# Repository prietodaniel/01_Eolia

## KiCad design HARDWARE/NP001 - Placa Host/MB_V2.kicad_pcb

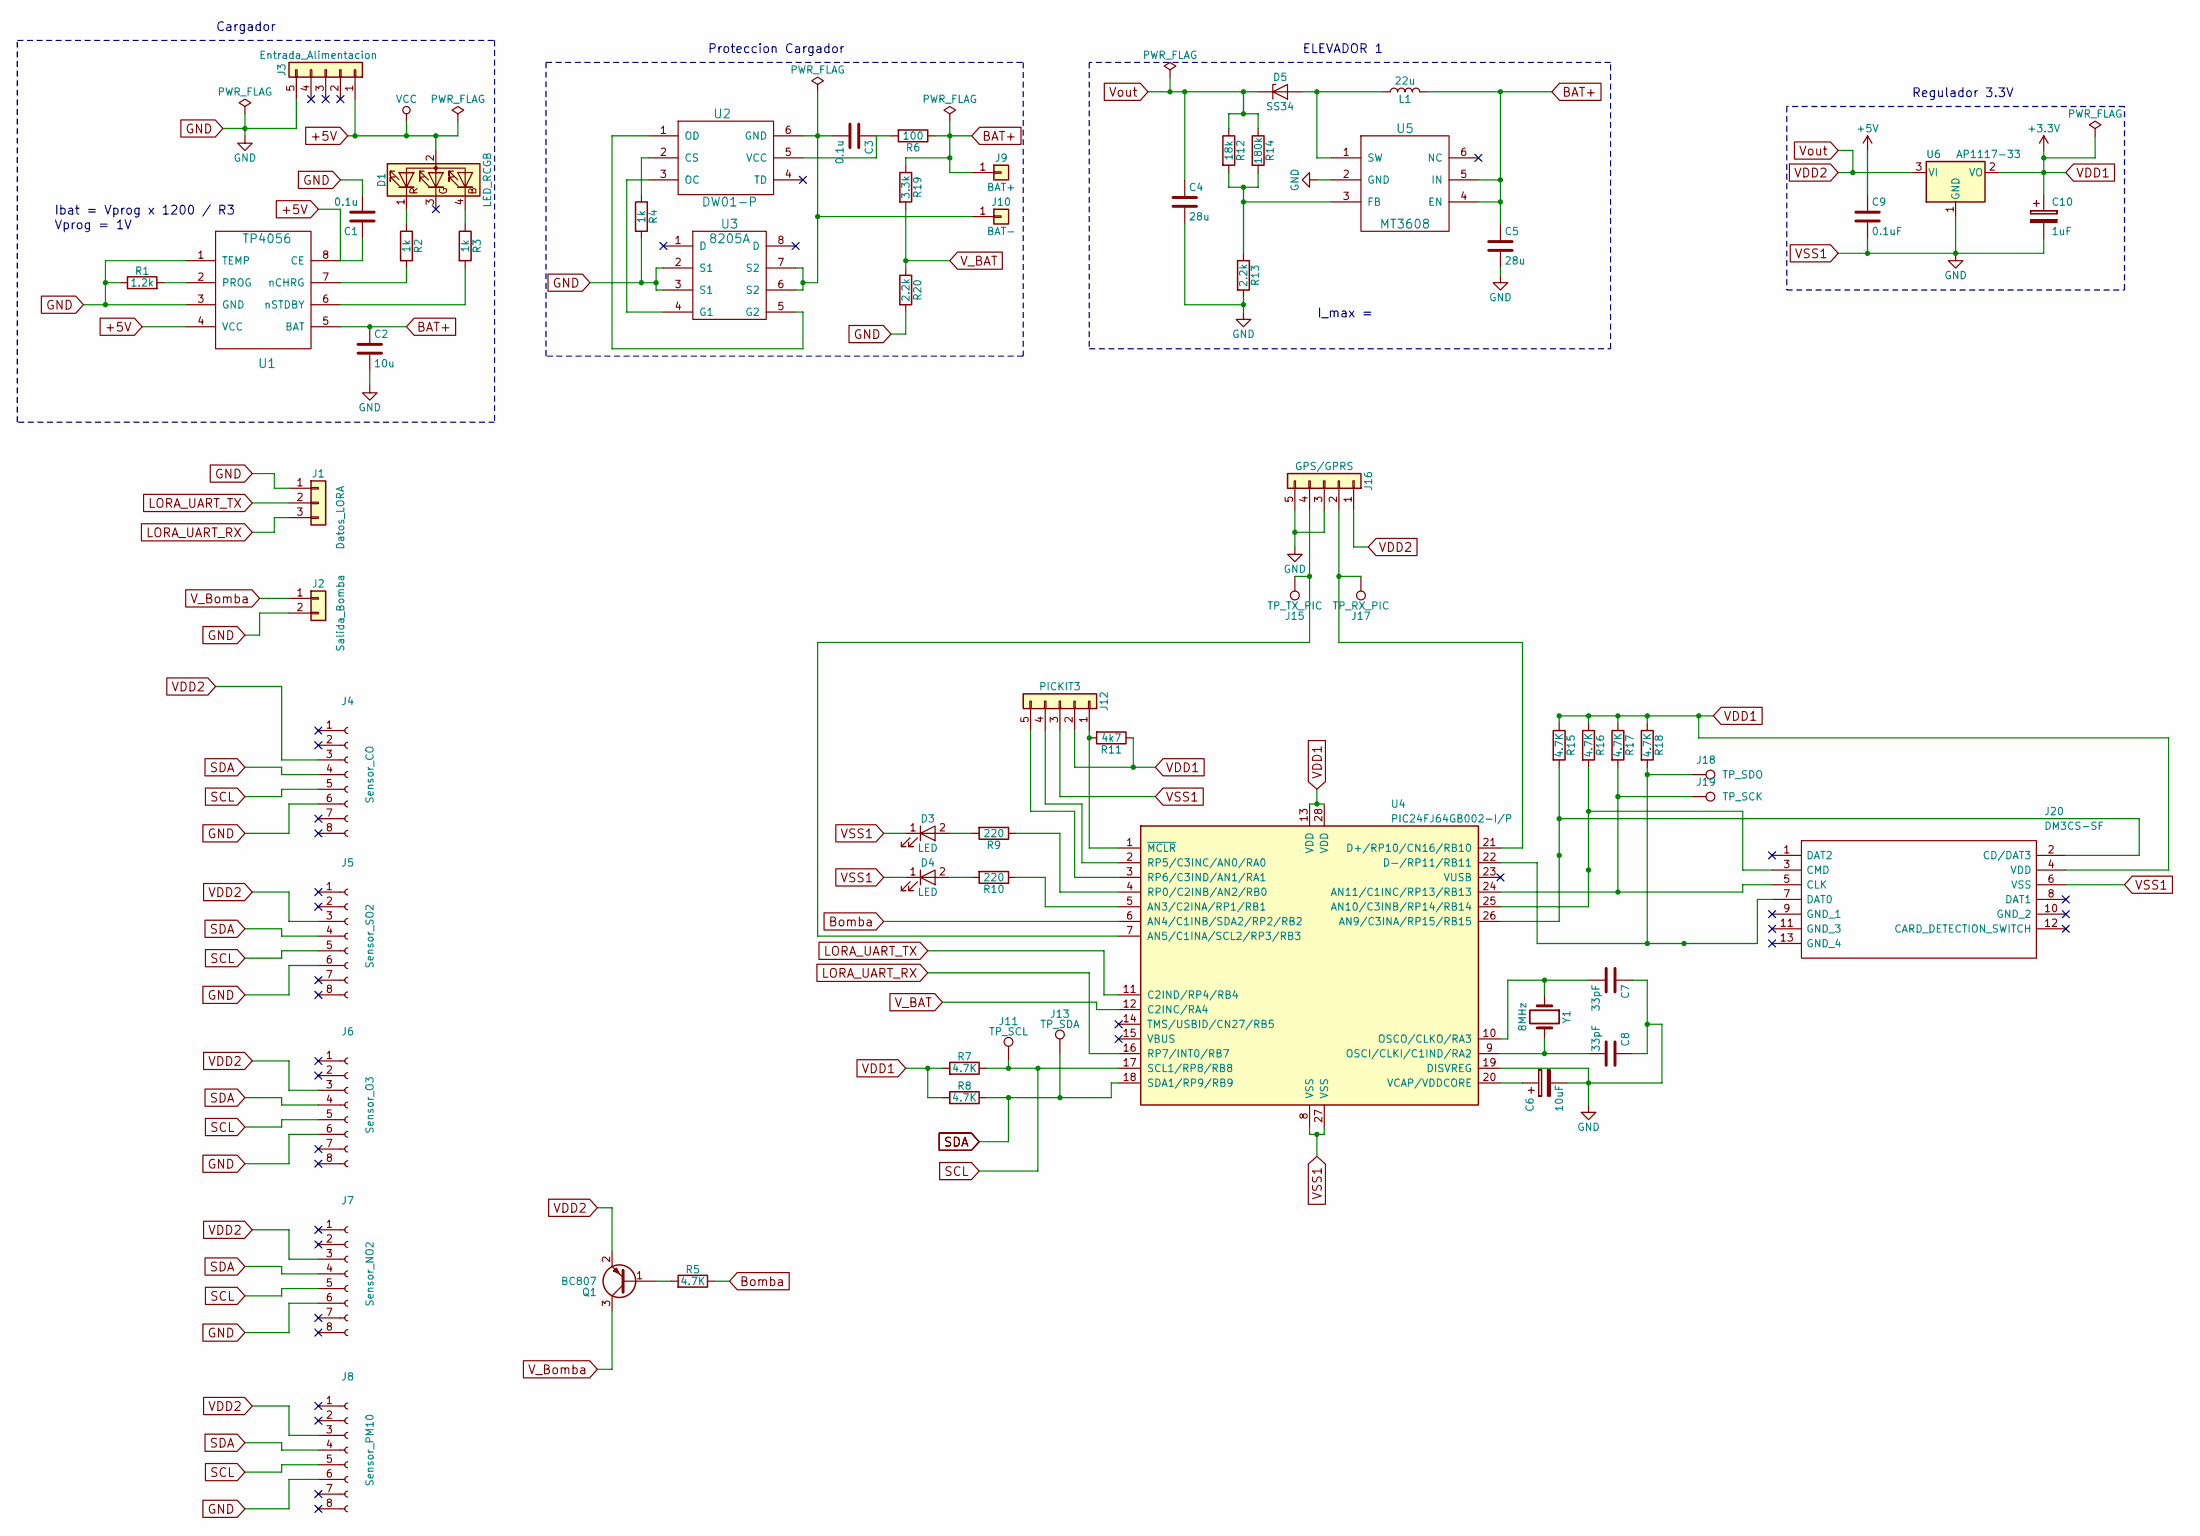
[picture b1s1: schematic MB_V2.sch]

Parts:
C1, C3: 0.1u; C_0805
C2: 10u; C_0805
C4, C5: 28u; C_1206
C6: 10uF; CP_Tantalum_Case-B_EIA-3528-21_Hand
C7, C8: 33pF; C_0805_HandSoldering
C9: 0.1uF; CP_Tantalum_Case-B_EIA-3528-21_Hand
C10: 1uF; CP_Tantalum_Case-B_EIA-3528-21_Hand
D1: LED_RCGB; LED_D5.0mm-4
D3, D4: LED; LED_D3.0mm_Horizontal_O1.27mm_Z2.0mm
D5: SS34; D_SMC
J1: Datos_LORA; JST_PH_B3B-PH-SM4-TB_03x2.00mm_Straight
J2: Salida_Bomba; JST_PH_B2B-PH-SM4-TB_02x2.00mm_Straight
J3: Entrada_Alimentacion; USB_Micro-B_Molex_47346-0001
J4: Sensor_CO; Socket_Strip_Angled_1x08_Pitch2.54mm
J5: Sensor_SO2; Socket_Strip_Angled_1x08_Pitch2.54mm
J6: Sensor_O3; Socket_Strip_Angled_1x08_Pitch2.54mm
J7: Sensor_NO2; Socket_Strip_Angled_1x08_Pitch2.54mm
J8: Sensor_PM10; Socket_Strip_Angled_1x08_Pitch2.54mm
J9: BAT+; MountingHole_2.2mm_M2_DIN965_Pad
J10: BAT-; MountingHole_2.2mm_M2_DIN965_Pad
J11: TP_SCL; PINTST
J12: PICKIT3; Pin_Header_Straight_1x05_Pitch2.54mm
J13: TP_SDA; PINTST
J15: TP_TX_PIC; PINTST
J16: GPS/GPRS; JST_PH_B5B-PH-SM4-TB_05x2.00mm_Straight
J17: TP_RX_PIC; PINTST
J18: TP_SDO; PINTST
J19: TP_SCK; PINTST
J20: DM3CS-SF; SD_CARD_DP; Mouser Part Number 798-DM3CSSF
L1: 22u; L_10.4x10.4_H4.8
Q1: BC807; SOT-23
R1: 1.2k; R_0805
R2, R3, R4: 1k; R_0805
R5, R7, R8, R15, R16, R17, R18: 4.7K; R_0805_HandSoldering
R6: 100; R_0805
R9, R10: 220; R_0805_HandSoldering
R11: 4k7; R_0805_HandSoldering
R12: 18k; R_0805
R13, R20: 2.2k; R_0805
R14: 180k; R_0805
R19: 3.3k; R_0805
U1: TP4056; SOIC-8_3.9x4.9mm_Pitch1.27mm
U2: DW01-P; TSOP-6_1.65x3.05mm_Pitch0.95mm
U3: 8205A; TSSOP-8_4.4x3mm_Pitch0.65mm
U4: PIC24FJ64GB002-I/P; SOIC-28W_7.5x17.9mm_Pitch1.27mm
U5: MT3608; TSOP-6_1.65x3.05mm_Pitch0.95mm
U6: AP1117-33; SOT-223-3_TabPin2
Y1: 8MHz; Crystal_SMD_HC49-SD_HandSoldering

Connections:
+5V: C1.1, C9.1, D1.2 (A), J3.1, U1.4 (VCC), U1.8 (CE)
BAT+: C2.1, C5.1, J9.1, L1.2, R6.1, R19.1, U1.5 (BAT), U5.4 (EN), U5.5 (IN)
Bomba: R5.1, U4.6 (AN4/C1INB/SDA2/RP2/RB2)
GND: C1.2, C2.2, C4.2, C5.2, C6.2, C7.1, C8.1, C9.2, C10.2, D3.1 (K), D4.1 (K), J1.1, J2.2, J3.5, J4.6, J5.6, J6.6, J7.6, J8.6, J12.3, J16.3, J16.5, J20.6 (VSS), R1.1, R4.2, R13.2, R20.2, U1.1 (TEMP), U1.3 (GND), U3.2 (S1), U3.3 (S1), U4.8 (VSS), U4.19 (DISVREG), U4.27 (VSS), U5.2 (GND), U6.1 (GND)
LORA_UART_RX: J1.3, U4.16 (RP7/INT0/RB7)
LORA_UART_TX: J1.2, U4.11 (C2IND/RP4/RB4)
unnamed: C3.1, R6.2, U2.5 (VCC)
unnamed: C3.2, J10.1, U2.6 (GND), U3.6 (S2), U3.7 (S2)
unnamed: C6.1, U4.20 (VCAP/VDDCORE)
unnamed: C7.2, U4.10 (OSCO/CLKO/RA3), Y1.1
unnamed: C8.2, U4.9 (OSCI/CLKI/C1IND/RA2), Y1.2
unnamed: D1.1 (RK), R2.1
unnamed: D1.4 (BK), R3.1
unnamed: D3.2 (A), R9.2
unnamed: D4.2 (A), R10.2
unnamed: D5.2 (A), L1.1, U5.1 (SW)
unnamed: J12.1, R11.2, U4.1 (~MCLR~)
unnamed: J12.4, U4.2 (RP5/C3INC/AN0/RA0)
unnamed: J12.5, U4.3 (RP6/C3IND/AN1/RA1)
unnamed: J15.1, J16.4, U4.7 (AN5/C1INA/SCL2/RP3/RB3)
unnamed: J16.2, J17.1, U4.21 (D+/RP10/CN16/RB10)
unnamed: J18.1, J20.7 (DAT0), R18.2, U4.22 (D-/RP11/RB11)
unnamed: J19.1, J20.5 (CLK), R17.2, U4.24 (AN11/C1INC/RP13/RB13)
unnamed: J20.2 (CD/DAT3), R15.2, U4.26 (AN9/C3INA/RP15/RB15)
unnamed: J20.3 (CMD), R16.2, U4.25 (AN10/C3INB/RP14/RB14)
unnamed: Q1.1 (B), R5.2
unnamed: R1.2, U1.2 (PROG)
unnamed: R2.2, U1.7 (nCHRG)
unnamed: R3.2, U1.6 (nSTDBY)
unnamed: R4.1, U2.2 (CS)
unnamed: R9.1, U4.4 (RP0/C2INB/AN2/RB0)
unnamed: R10.1, U4.5 (AN3/C2INA/RP1/RB1)
unnamed: R12.2, R13.1, R14.2, U5.3 (FB)
unnamed: U2.1 (OD), U3.5 (G2)
unnamed: U2.3 (OC), U3.4 (G1)
SCL: J4.5, J5.5, J6.5, J7.5, J8.5, J11.1, R7.1, U4.17 (SCL1/RP8/RB8)
SDA: J4.4, J5.4, J6.4, J7.4, J8.4, J13.1, R8.1, U4.18 (SDA1/RP9/RB9)
VDD1: C10.1, J12.2, J20.4 (VDD), R7.2, R8.2, R11.1, R15.1, R16.1, R17.1, R18.1, U4.13 (VDD), U4.28 (VDD), U6.2 (VO)
VDD2: C4.1, D5.1 (K), J4.3, J5.3, J6.3, J7.3, J8.3, J16.1, Q1.2 (E), R12.1, R14.1, U6.3 (VI)
V_BAT: R19.2, R20.1, U4.12 (C2INC/RA4)
V_Bomba: J2.1, Q1.3 (C)

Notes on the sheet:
Ibat = Vprog x 1200 / R3
Vprog = 1V
ELEVADOR 1
Proteccion Cargador
Cargador
I_max =
Regulador 3.3V

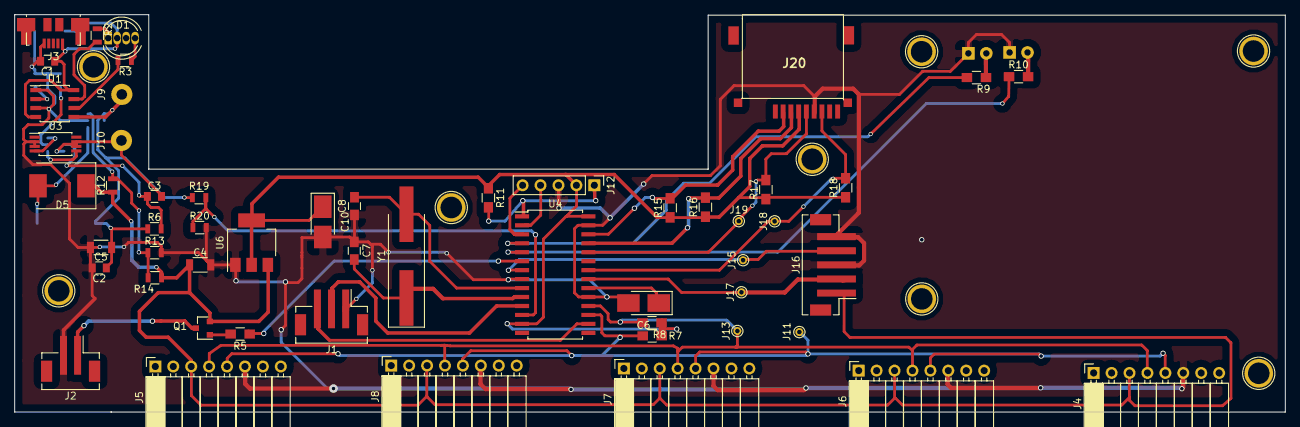
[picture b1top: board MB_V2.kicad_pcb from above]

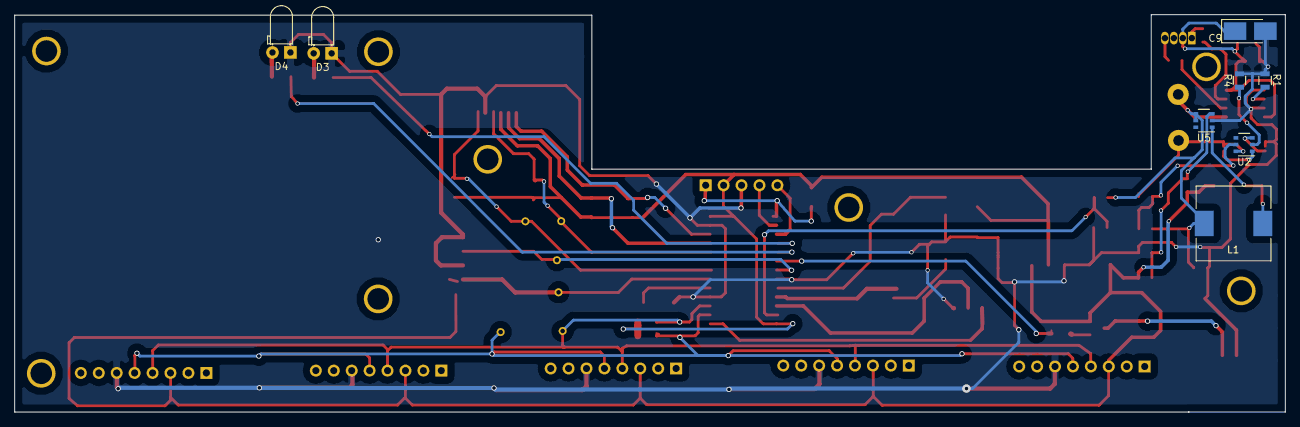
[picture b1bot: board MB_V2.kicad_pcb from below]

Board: 2 copper layers, 180.1 x 56.3 mm, 62 parts (8 on the bottom side), 41 nets.

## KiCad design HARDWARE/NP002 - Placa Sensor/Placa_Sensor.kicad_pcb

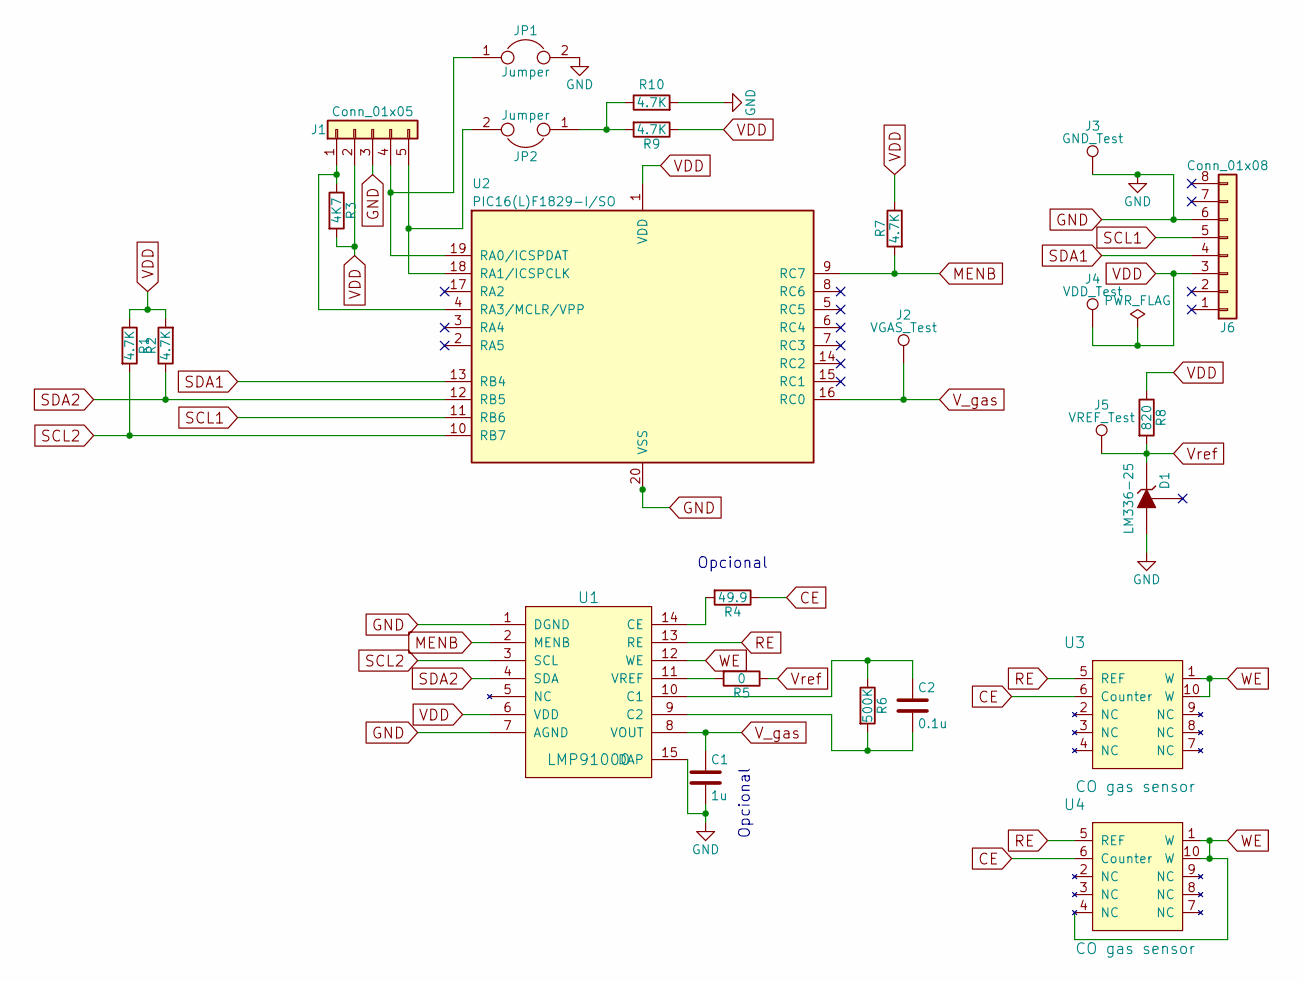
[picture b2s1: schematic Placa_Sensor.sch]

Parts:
C1: 1u; C_1206_HandSoldering
C2: 0.1u; C_0805_HandSoldering
D1: LM336-25; TO-92_Inline_Wide
J1: Conn_01x05; Pin_Header_Straight_1x05_Pitch2.54mm
J2: VGAS_Test; PINTST
J3: GND_Test; PINTST
J4: VDD_Test; PINTST
J5: VREF_Test; PINTST
J6: Conn_01x08; Pin_Header_Straight_1x08_Pitch2.54mm
JP1, JP2: Jumper; Pin_Header_Straight_1x02_Pitch2.54mm
R1, R2, R7, R9, R10: 4.7K; R_0805_HandSoldering
R3: 4K7; R_0805_HandSoldering
R4: 49.9; R_0805_HandSoldering
R5: 0; R_0805_HandSoldering
R6: 500K; R_0805_HandSoldering
R8: 820; R_0805_HandSoldering
U1: LMP91000; WSON-14_1EP_4.0x4.0mm_Pitch0.5mm
U2: PIC16(L)F1829-I/SO; SOIC-20W_7.5x12.8mm_Pitch1.27mm
U3: CO gas sensor; SPEC_Gas_Sensor_C_Package_THT_4pins; MPN 110-109; Digi-Key_PN 1684-1001-ND
U4: CO gas sensor; SPEC_Gas_Sensor_P_Package; MPN 110-109; Digi-Key_PN 1684-1001-ND

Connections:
CE: R4.1, U3.6 (Counter), U4.6 (Counter)
GND: C1.2, D1.2 (A), J1.3, J3.1, J6.6, JP1.2, R10.2, U1.1 (DGND), U1.7 (AGND), U1.15 (DAP), U2.20 (VSS)
MENB: R7.2, U1.2 (MENB), U2.9 (RC7)
unnamed: C2.1, R6.1, U1.10 (C1)
unnamed: C2.2, R6.2, U1.9 (C2)
unnamed: J1.1, R3.1, U2.4 (RA3/MCLR/VPP)
unnamed: J1.4, JP1.1, U2.19 (RA0/ICSPDAT)
unnamed: J1.5, JP2.2, U2.18 (RA1/ICSPCLK)
unnamed: JP2.1, R9.2, R10.1
unnamed: R4.2, U1.14 (CE)
unnamed: R5.2, U1.11 (VREF)
RE: U1.13 (RE), U3.5 (REF), U4.5 (REF)
SCL1: J6.5, U2.11 (RB6)
SCL2: R1.2, U1.3 (SCL), U2.10 (RB7)
SDA1: J6.4, U2.13 (RB4)
SDA2: R2.1, U1.4 (SDA), U2.12 (RB5)
VDD: J1.2, J4.1, J6.3, R1.1, R2.2, R3.2, R7.1, R8.1, R9.1, U1.6 (VDD), U2.1 (VDD)
V_gas: C1.1, J2.1, U1.8 (VOUT), U2.16 (RC0)
Vref: D1.1 (K), J5.1, R5.1, R8.2
WE: U1.12 (WE), U3.1 (W), U3.10 (W), U4.1 (W), U4.4 (NC), U4.10 (W)

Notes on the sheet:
Opcional

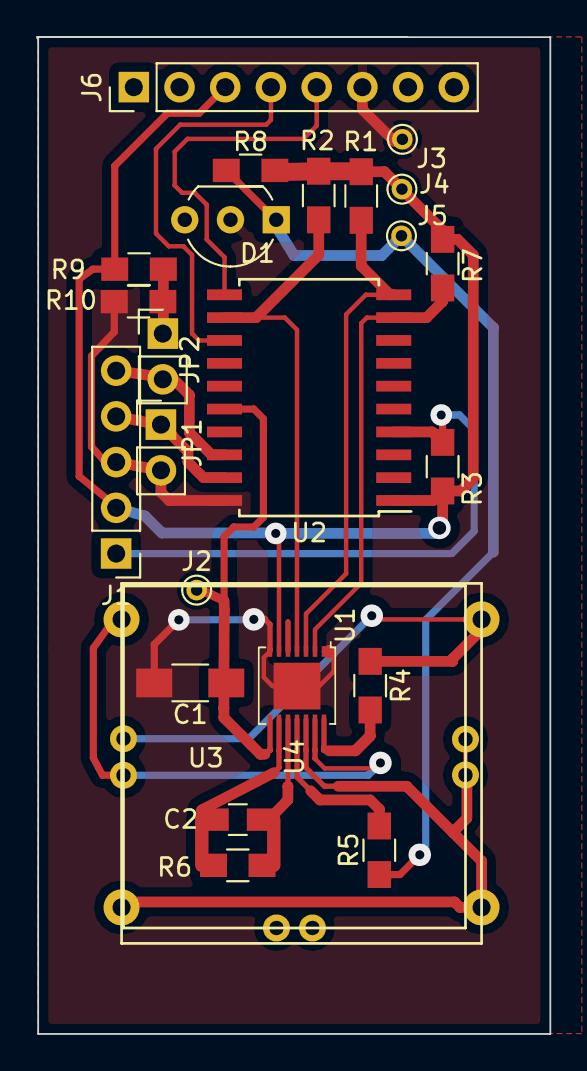
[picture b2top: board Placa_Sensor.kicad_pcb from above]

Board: 2 copper layers, 28.5 x 55.4 mm, 25 parts (0 on the bottom side), 20 nets.

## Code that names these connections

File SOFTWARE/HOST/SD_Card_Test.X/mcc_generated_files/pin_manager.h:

/**
  System Interrupts Generated Driver File

  @Company:
    Microchip Technology Inc.

  @File Name:
    pin_manager.h

  @Summary:
    This is the generated manager file for the MPLAB(c) Code Configurator device.  This manager
    configures the pins direction, initial state, analog setting.
    The peripheral pin select, PPS, configuration is also handled by this manager.

  @Description:
    This source file provides implementations for MPLAB(c) Code Configurator interrupts.
    Generation Information :
        Product Revision  :  MPLAB(c) Code Configurator - 4.45
        Device            :  PIC24FJ64GB002
    The generated drivers are tested against the following:
        Compiler          :  XC16 1.32
        MPLAB             :  MPLAB X 3.61

    Copyright (c) 2013 - 2015 released Microchip Technology Inc.  All rights reserved.

    Microchip licenses to you the right to use, modify, copy and distribute
    Software only when embedded on a Microchip microcontroller or digital signal
    controller that is integrated into your product or third party product
    (pursuant to the sublicense terms in the accompanying license agreement).

    You should refer to the license agreement accompanying this Software for
    additional information regarding your rights and obligations.

    SOFTWARE AND DOCUMENTATION ARE PROVIDED "AS IS" WITHOUT WARRANTY OF ANY KIND,
    EITHER EXPRESS OR IMPLIED, INCLUDING WITHOUT LIMITATION, ANY WARRANTY OF
    MERCHANTABILITY, TITLE, NON-INFRINGEMENT AND FITNESS FOR A PARTICULAR PURPOSE.
    IN NO EVENT SHALL MICROCHIP OR ITS LICENSORS BE LIABLE OR OBLIGATED UNDER
    CONTRACT, NEGLIGENCE, STRICT LIABILITY, CONTRIBUTION, BREACH OF WARRANTY, OR
    OTHER LEGAL EQUITABLE THEORY ANY DIRECT OR INDIRECT DAMAGES OR EXPENSES
    INCLUDING BUT NOT LIMITED TO ANY INCIDENTAL, SPECIAL, INDIRECT, PUNITIVE OR
    CONSEQUENTIAL DAMAGES, LOST PROFITS OR LOST DATA, COST OF PROCUREMENT OF
    SUBSTITUTE GOODS, TECHNOLOGY, SERVICES, OR ANY CLAIMS BY THIRD PARTIES
    (INCLUDING BUT NOT LIMITED TO ANY DEFENSE THEREOF), OR OTHER SIMILAR COSTS.

*/

#ifndef _PIN_MANAGER_H
#define _PIN_MANAGER_H
/**
    Section: Includes
*/
#include <xc.h>
/**
    Section: Device Pin Macros
*/

#define INPUT   1
#define OUTPUT  0

#define HIGH    1
#define LOW     0

#define ANALOG      1
#define DIGITAL     0

#define PULL_UP_ENABLED      1
#define PULL_UP_DISABLED     0

/*
  @Example
    <code>
    // Set RB11 high (1)
    SS1OUT_SetHigh();
    </code>
*/

#define SD_CS_TRIS               TRISC0
#define SD_CS_LAT                LATC0
#define SD_CS_PORT               PORTCbits.RC0

#define SD_CS_SetHigh()          _LATB11 = 1
#define SD_CS_SetLow()           _LATB11 = 0
#define SD_CS_Toggle()           _LATB11 ^= 1
#define SD_CS_GetValue()         _RB11
#define SD_CS_SetDigitalInput()  _TRISB11 = 1
#define SD_CS_SetDigitalOutput() _TRISB11 = 0

/*
  @Example
    <code>
    // Set RB13 high (1)
    SDO1_SetHigh();
    </code>

*/
#define SDO1_SetHigh()          _LATB13 = 1
/*
  @Example
    <code>
    // Set RB13 low (0)
    SDO1_SetLow();
    </code>

*/
#define SDO1_SetLow()           _LATB13 = 0
/*
  @Example
    <code>
    // Toggle RB13
    SDO1_Toggle();
    </code>

*/
#define SDO1_Toggle()           _LATB13 ^= 1
/*
  @Example
    <code>
    uint16_t portValue;

    // Read RB13
    postValue = SDO1_GetValue();
    </code>

*/
#define SDO1_GetValue()         _RB13
/*
  @Example
    <code>
    // Sets the RB13 as an input
    SDO1_SetDigitalInput();
    </code>

*/
#define SDO1_SetDigitalInput()  _TRISB13 = 1
/*
  @Example
    <code>
    // Sets the RB13 as an output
    SDO1_SetDigitalOutput();
    </code>

*/
#define SDO1_SetDigitalOutput() _TRISB13 = 0
/*
  @Example
    <code>
    // Set RB14 high (1)
    SDI1_SetHigh();
    </code>

*/
#define SDI1_SetHigh()          _LATB14 = 1
/*
  @Example
    <code>
    // Set RB14 low (0)
    SDI1_SetLow();
    </code>

*/
#define SDI1_SetLow()           _LATB14 = 0
/*
  @Example
    <code>
    // Toggle RB14
    SDI1_Toggle();
    </code>

*/
#define SDI1_Toggle()           _LATB14 ^= 1
/*
  @Example
    <code>
    uint16_t portValue;

    // Read RB14
    postValue = SDI1_GetValue();
    </code>

*/
#define SDI1_GetValue()         _RB14
/*

  @Example
    <code>
    // Sets the RB14 as an input
    SDI1_SetDigitalInput();
    </code>

*/
#define SDI1_SetDigitalInput()  _TRISB14 = 1
/*
  @Example
    <code>
    // Sets the RB14 as an output
    SDI1_SetDigitalOutput();
    </code>

*/
#define SDI1_SetDigitalOutput() _TRISB14 = 0
/*
  @Example
    <code>
    // Set RB15 high (1)
    SCK1OUT_SetHigh();
    </code>

*/
#define SCK1OUT_SetHigh()          _LATB15 = 1
/*
  @Example
    <code>
    // Set RB15 low (0)
    SCK1OUT_SetLow();
    </code>

*/
#define SCK1OUT_SetLow()           _LATB15 = 0
/*
  @Example
    <code>
    // Toggle RB15
    SCK1OUT_Toggle();
    </code>

*/
#define SCK1OUT_Toggle()           _LATB15 ^= 1
/*
    // Read RB15
    postValue = SCK1OUT_GetValue();
    </code>

*/
#define SCK1OUT_GetValue()         _RB15
/*
  @Example
    <code>
    // Sets the RB15 as an input
    SCK1OUT_SetDigitalInput();
    </code>

*/
#define SCK1OUT_SetDigitalInput()  _TRISB15 = 1
/*
  @Example
    <code>
    // Sets the RB15 as an output
    SCK1OUT_SetDigitalOutput();
    </code>

*/
#define SCK1OUT_SetDigitalOutput() _TRISB15 = 0

/*
  @Example
    <code>
    void SYSTEM_Initialize(void)
    {
        // Other initializers are called from this function
        PIN_MANAGER_Initialize();
    }
    </code>

*/
void PIN_MANAGER_Initialize(void);

#endif

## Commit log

2019-09-17 asd
    asdsds
2019-12-04 Daniel Prieto:
    -Subo placa enviada a China.
